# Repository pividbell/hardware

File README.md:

# pividbell - the Raspberry Pi Video Doorbell

This is a work-in-progress smart doorbell, powered by a Pi 0W.

## Progress

Progress is tracked through #1. So far, no hardware prototypes have been built. 

## Planned Features

These features have not yet been implemented, and as such implementation details may change later on.

* Video streaming with night vision (using Pi Camera) - RTSP feed for integration with NVRs such as Frigate.
* Intercom functionality - likely as a SIP phone that rings a predetermined extension when doorbell pressed.
* Optional NFC - intended for monitoring people coming and going for home automation platforms. [^1]
* Optional door release & status - the ability to drive a solenoid to open a door and a reed switch to determine if a door is open or not. [^2]
* Addressable RGB ~~for gamers~~ to indicate button position and provide feedback.

## Hardware Design

The schematics and PCBs can be found in the [pcbs](pcbs/) directory. Hardware design is done with [KiCAD EDA](https://www.kicad.org/).

### General background

The doorbell is powered by a Pi Zero W, with power and all connections being provided over its 40-pin GPIO header. A Pi NoIR camera, combined with several IR LEDs, provides the video feed and night vision capabilities. Audio input and output is handled by a I<sup>2</sup>S ADC and DAC respectively.

**Warning:** 'Dumb' doorbells in the UK and US are commonly powered by AC voltage - **this doorbell will not work correctly on AC - it requires a 12V DC input.**

### Button

This doorbell uses a capactive button, rather than a physical one. This has a few benefits, including:

* Capacitive button tends to be cheaper than a water resistant pushbutton
* Fewer points of water ingress
* Theoretically, better longevity - though most water resistant pushbuttons are also rated for very high number of cycles, so this is not as important

Once the doorbell prototype has been fabricated and assembled, the possibility of a contactless doorbell (ie, configuring the capacitive controller to be more sensitive to trigger if approached to within a centimetre or two) will also be investigated. This could reduce fingerprints and reduce cleaning requirements.

## Case Design

This will be a recessed doorbell, re-using the recess box of an existing (and in my case, already installed) doorbell. This section of the README will be expanded further once the housing has been designed.

[^1]: This should not be considered secure; whilst it *could* conceivably be used as authentication for the door release functionality, it is strongly recommended against.
[^2]: Again, this may not be secure - similar to many commercially available doorbells, it would be possible to open the doorbell (with the correct tools) and simply short the wires to trigger the door release.

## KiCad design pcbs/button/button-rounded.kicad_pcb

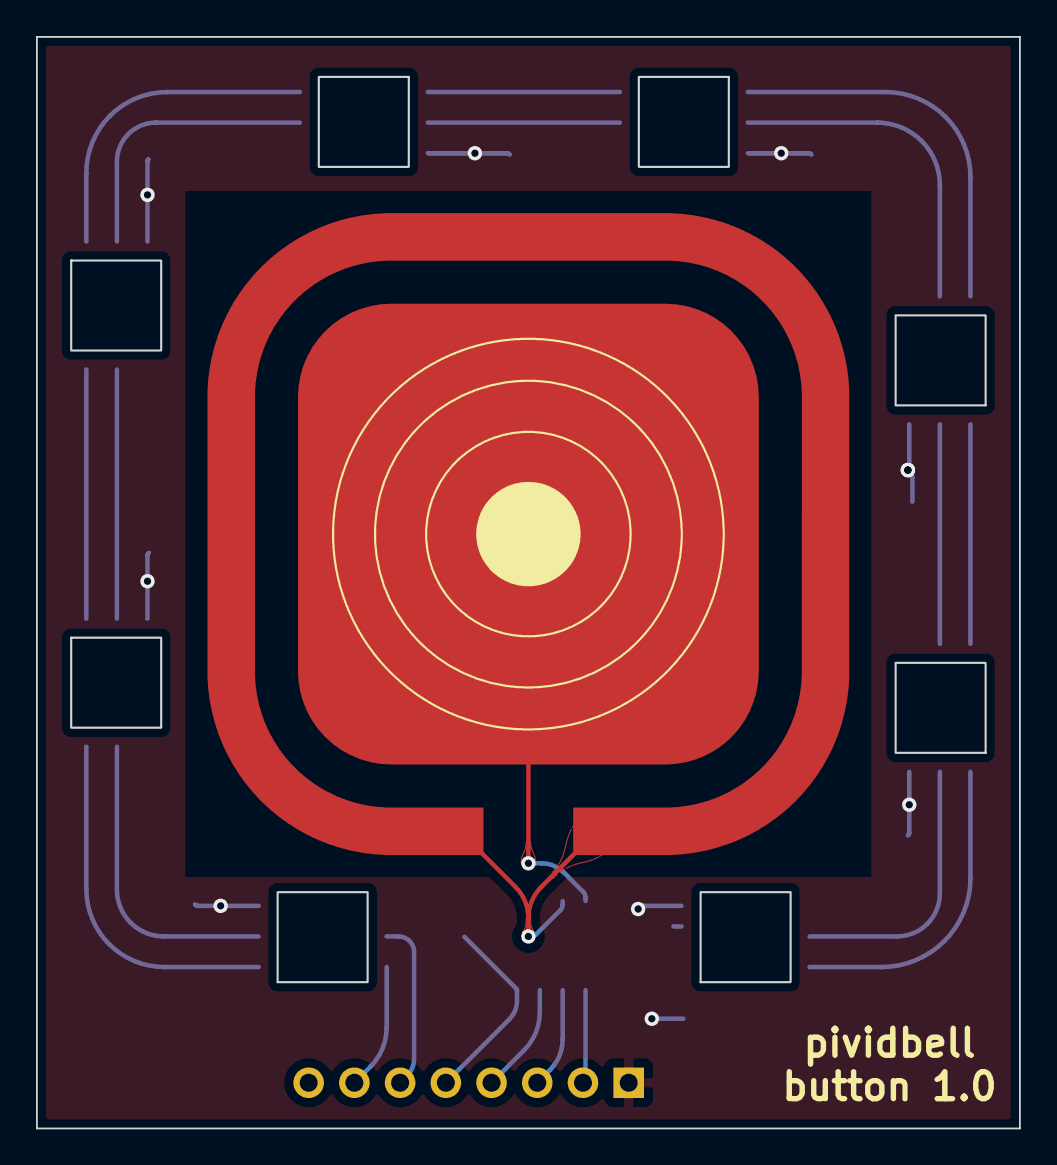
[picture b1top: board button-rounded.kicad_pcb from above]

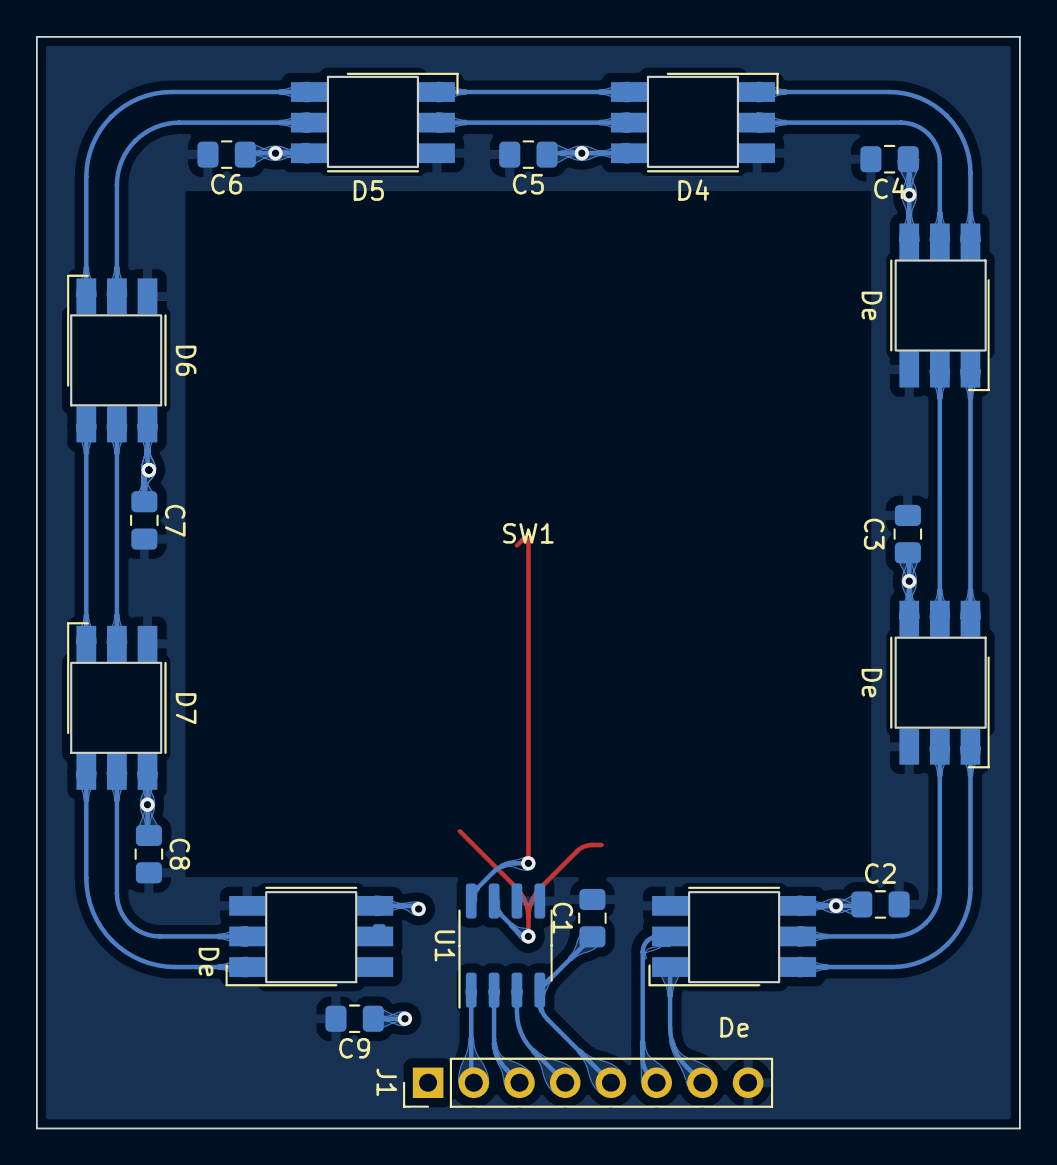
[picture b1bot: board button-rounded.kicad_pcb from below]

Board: 2 copper layers, 54.6 x 60.6 mm, 20 parts (19 on the bottom side), 24 nets.

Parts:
C1, C2, C3, C4, C5, C6, C7, C8, C9: 10n; C_0805_2012Metric_Pad1.18x1.45mm_HandSolder
D4, D5, D6, D7: APA102; LED_RGB_5050-6-flipped
De: APA102; LED_RGB_5050-6-flipped
De#2, De#3, De#4: APA102; LED_RGB_5050-6-flipped
J1: Conn_01x08; PinHeader_1x08_P2.54mm_Vertical
SW1: CAP-BUTTON; button-internal
U1: CAP1293; SOIC-8_3.9x4.9mm_P1.27mm

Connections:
+3V3: C1.1, J1.5, U1.4 (VDD)
+5V: C2.1, C3.1, C4.1, C5.1, C6.1, C7.1, C8.1, C9.1, D4.4 (VCC), D5.4 (VCC), D6.4 (VCC), D7.4 (VCC), De.4 (VCC), De#2.4 (VCC), De#3.4 (VCC), De#4.4 (VCC), J1.1
/CAP_INT: J1.2, U1.1 (ALERT#)
/I2C_SCL: J1.4, U1.3 (SMCLK)
/I2C_SDA: J1.3, U1.2 (SMDATA)
/LED_DATA: De.1 (DI), J1.7
/LED_SCK: De.2 (CI), J1.6
GND: C1.2, C2.2, C3.2, C4.2, C5.2, C6.2, C7.2, C8.2, C9.2, D4.3 (GND), D5.3 (GND), D6.3 (GND), D7.3 (GND), De.3 (GND), De#2.3 (GND), De#3.3 (GND), De#4.3 (GND), J1.8, U1.5 (GND), U1.6 (CS3)
unnamed: De.5 (CO), De#2.2 (CI)
unnamed: De.6 (DO), De#2.1 (DI)
unnamed: De#2.5 (CO), De#4.2 (CI)
unnamed: De#2.6 (DO), De#4.1 (DI)
unnamed: D4.2 (CI), De#4.5 (CO)
unnamed: D4.1 (DI), De#4.6 (DO)
unnamed: D4.5 (CO), D5.2 (CI)
unnamed: D4.6 (DO), D5.1 (DI)
unnamed: D5.5 (CO), D6.2 (CI)
unnamed: D5.6 (DO), D6.1 (DI)
unnamed: D6.5 (CO), D7.2 (CI)
unnamed: D6.6 (DO), D7.1 (DI)
unnamed: D7.5 (CO), De#3.2 (CI)
unnamed: D7.6 (DO), De#3.1 (DI)
unnamed: SW1.1 (INNER), U1.8 (CS1)
unnamed: SW1.2 (OUTER), U1.7 (CS2/SG)

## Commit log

2022-12-13 Add initial readme
2022-12-13 Add gitignore for PCBs.
2022-12-13 Add DAC & output amp
2022-12-13 Add power input stage, add EEPROM for GPIO autoconfiguration.
2022-12-16 Add microphone ADC
2022-12-16 Add connector for button PCB, add IR LEDs
2022-12-16 Add separate PCB for button with capacitive controller.
2022-12-16 Add LEDs to button PCB.
2022-12-22 Add PCB for capacitive button
2022-12-22 Add teardrops to capacitive button PCB.
2022-12-24 Add door release functionality
2022-12-24 Update readme to include more project information.
2022-12-24 Add security note on NFC authentication, door release.
2022-12-24 Change pull-up method on door status sensor
2022-12-24 Add I2C headers
2022-12-24 Switch from RJ11 to screw terminals for power
2022-12-24 Add EDA info to readme
2022-12-24 Connect Pi to +5V
2022-12-24 remove outer border from touch pad silkscreen
2022-12-24 Add note about AC input
